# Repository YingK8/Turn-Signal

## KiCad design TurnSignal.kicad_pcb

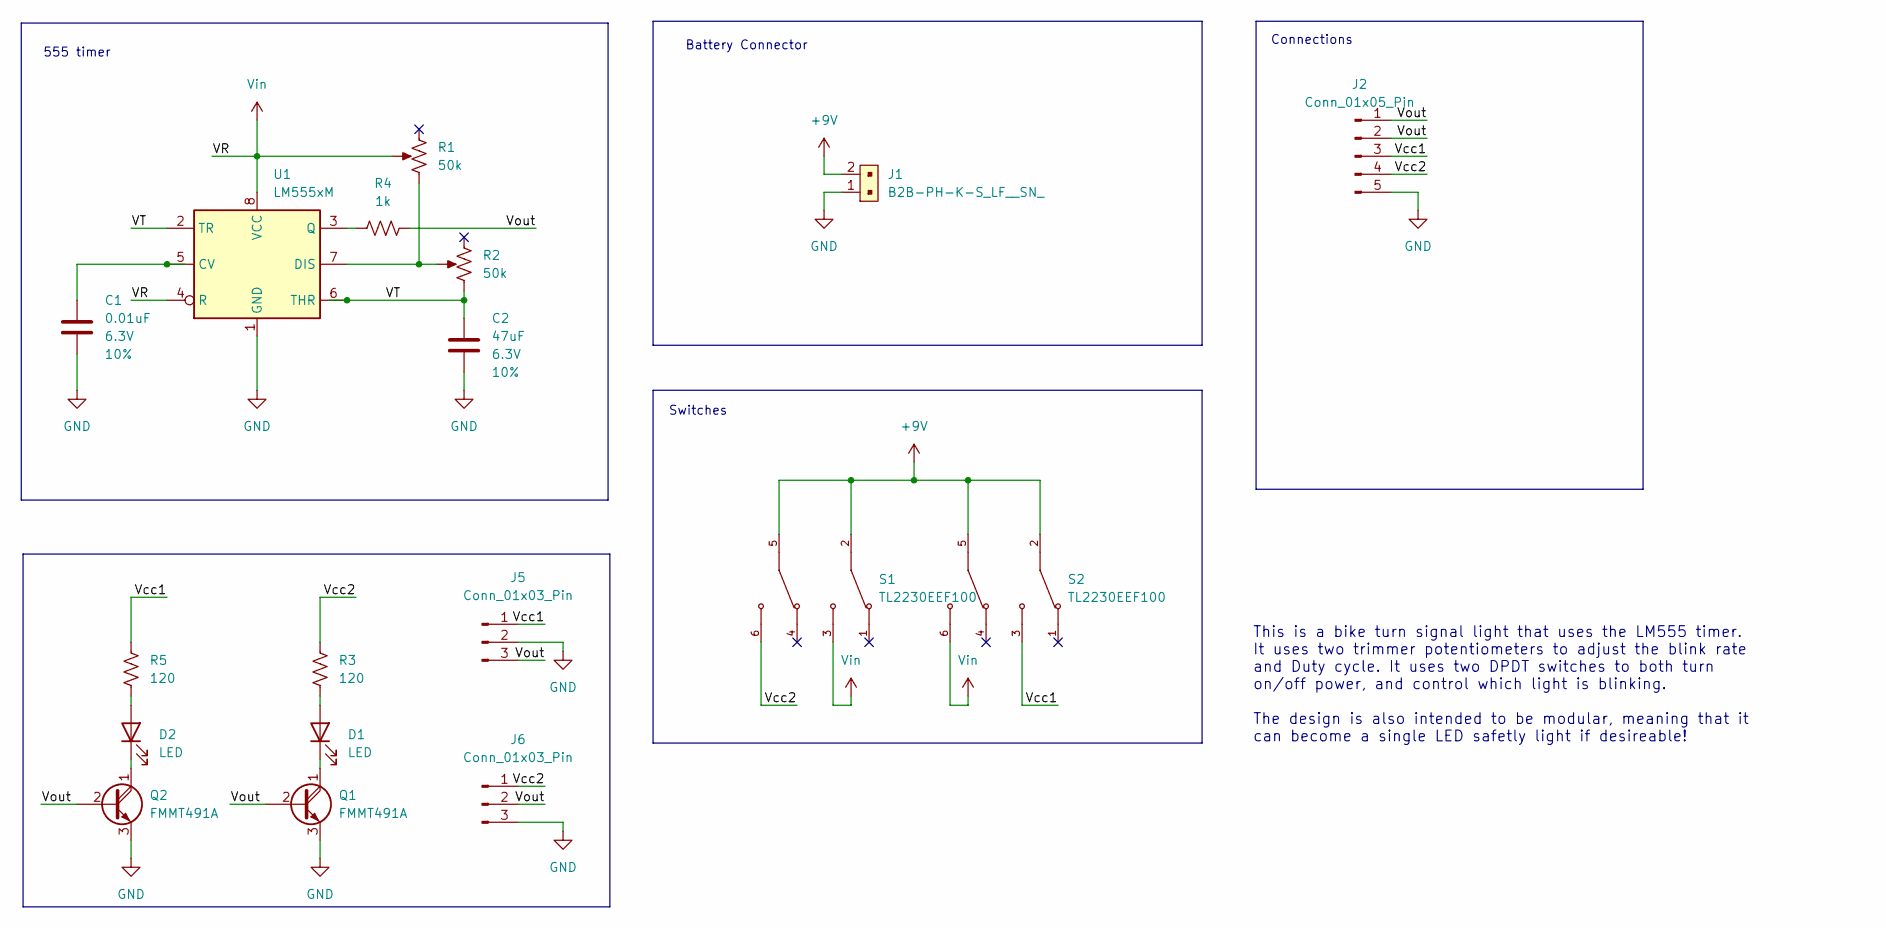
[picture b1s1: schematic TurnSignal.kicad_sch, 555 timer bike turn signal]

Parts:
C1: 0.01uF; C_0805_2012Metric_Pad1.18x1.45mm_HandSolder; Voltage 6.3V; Tolerance 10%
C2: 47uF; C_0805_2012Metric_Pad1.18x1.45mm_HandSolder; Voltage 6.3V; Tolerance 10%
D1, D2: LED; 4-PLCC LED
J1: B2B-PH-K-S_LF__SN_; PinHeader_1x2_P2mm_Drill1mm; MPN B2B-PH-K-S(LF)(SN); Digi-Key_PN 455-1704-ND
J2: Conn_01x05_Pin; PinHeader_1x05_P2.54mm_Vertical
J5, J6: Conn_01x03_Pin; PinHeader_1x03_P2.54mm_Vertical
Q1, Q2: FMMT491A; TO-92_Inline
R1, R2: 50k; TRIM_PV37W103C01B00; Mfg Part# 22AR10K
R3, R5: 120; C_0805_2012Metric_Pad1.18x1.45mm_HandSolder
R4: 1k; C_0805_2012Metric_Pad1.18x1.45mm_HandSolder
S1, S2: TL2230EEF100; SW_TL2230EEF100; PARTREV E
U1: LM555xM; SOIC-8_3.9x4.9mm_P1.27mm

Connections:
+9V: J1.2, S1.2, S1.5, S2.2, S2.5
/VT: C2.1, R2.1, U1.2 (TR), U1.6 (THR)
/Vcc1: J2.3, J5.1, R5.1, S2.3
/Vcc2: J2.4, J6.1, R3.1, S1.6
/Vout: J2.1, J2.2, J5.3, J6.2, Q1.2 (B), Q2.2 (B), R4.2
GND: C1.2, C2.2, J1.1, J2.5, J5.2, J6.3, Q1.3 (E), Q2.3 (E), U1.1 (GND)
unnamed: D1.2 (A), R3.2
unnamed: D1.1 (K), Q1.1 (C)
unnamed: D2.2 (A), R5.2
unnamed: D2.1 (K), Q2.1 (C)
unnamed: C1.1, U1.5 (CV)
unnamed: R1.1, R2.2, U1.7 (DIS)
unnamed: R4.1, U1.3 (Q)
Vin: R1.2, S1.3, S2.6, U1.4 (R), U1.8 (VCC)

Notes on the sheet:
Switches
555 timer
Connections
Battery Connector
This is a bike turn signal light that uses the LM555 timer. It uses two trimmer potentiometers to adjust the blink rate and Duty cycle. It uses two DPDT switches to both turn on/off power, and control which light is blinking. The design is also intended to be modular, meaning that it can become a s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

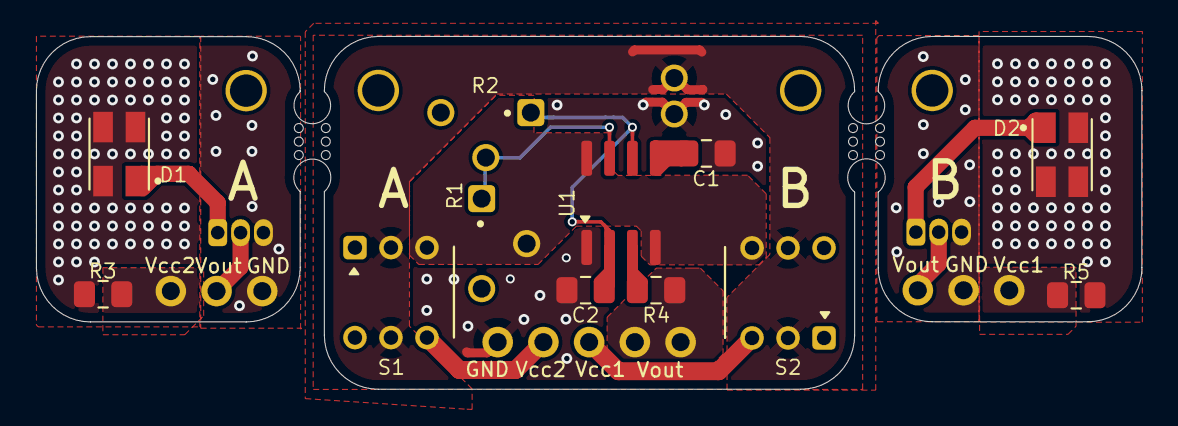
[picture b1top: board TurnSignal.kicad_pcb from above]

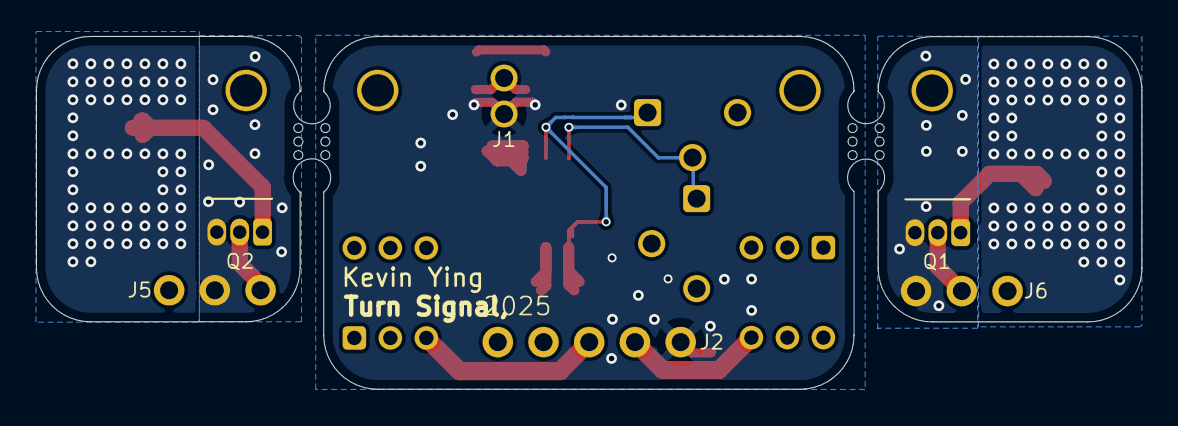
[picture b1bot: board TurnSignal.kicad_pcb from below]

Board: 2 copper layers, 61.4 x 19.6 mm, 20 parts (3 on the bottom side), 14 nets.

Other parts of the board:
mouse-bite-2mm-slot, mouse-bite-2mm-slot#2: VAL**; mouse-bite-2mm-slot

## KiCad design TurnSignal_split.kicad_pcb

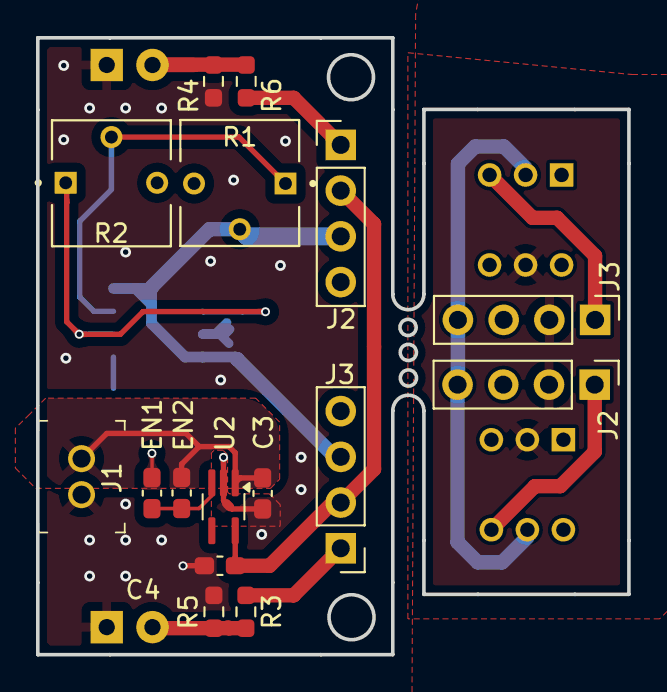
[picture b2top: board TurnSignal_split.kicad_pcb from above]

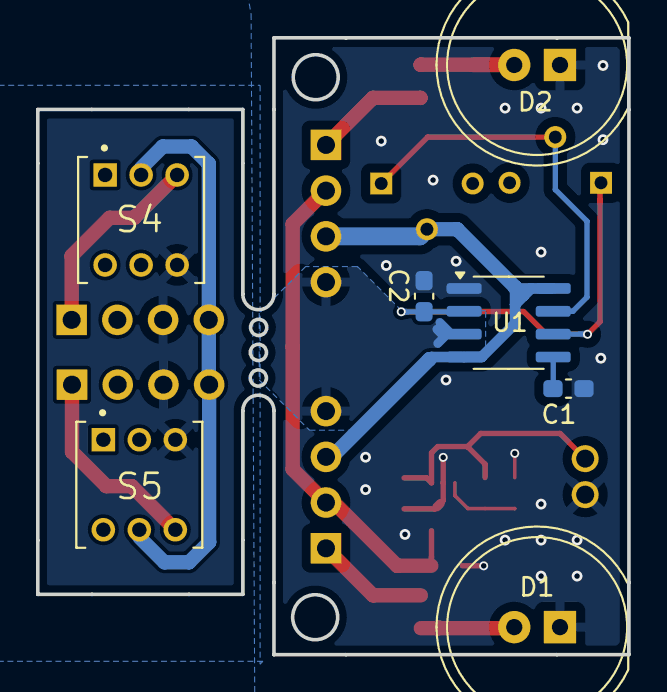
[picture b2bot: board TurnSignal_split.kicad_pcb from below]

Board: 2 copper layers, 32.8 x 34.3 mm, 23 parts (7 on the bottom side), 13 nets.

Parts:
C1: 0.01uF; C_0603_1608Metric_Pad1.08x0.95mm_HandSolder
C2: 470uF; C_0603_1608Metric_Pad1.08x0.95mm_HandSolder
C3, C4: 1uF; C_0603_1608Metric_Pad1.08x0.95mm_HandSolder
D1, D2: LED; LED_D10.0mm
EN1, EN2: 0; C_0603_1608Metric_Pad1.08x0.95mm_HandSolder
J1: B2B-PH-K-S_LF__SN_; PinHeader_1x2_P2mm_Drill1mm
J2, J2#2, J3, J3#2: Conn_01x04_Pin; PinHeader_1x04_P2.54mm_Vertical
R1, R2: 10k; TRIM_3362P-1-103LF
R3, R4, R5, R6: 1.5k; R_0603_1608Metric_Pad0.98x0.95mm_HandSolder
S4, S5: TL2230EEF100; SW_TL2230EEF100
U1: LM555xM; SOIC-8_3.9x4.9mm_P1.27mm
U2: MIC5365-3.3YC5; SOT-353_SC-70-5_Handsoldering

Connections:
+3V3: C4.1, J2.2, J2#2.2, J3.2, J3#2.2, S4.5, S5.2, U2.5 (VOUT)
+3V7: C3.1, EN1.2, J1.2, U2.1 (VIN)
/S1: J3.1, J3#2.1, R3.1, S4.3
/S2: J2.1, J2#2.1, R4.1, S5.6
/VT: C2.1, R2.1, U1.2 (TR), U1.6 (THR)
/Vout: J2.4, J2#2.4, J3.4, J3#2.4, S4.2, S5.5, U1.3 (Q)
GND: C1.2, C2.2, C3.2, C4.2, D1.1 (K), D2.1 (K), EN2.1, J1.1, R5.2, R6.2, U1.1 (GND), U2.2 (GND)
unnamed: D1.2 (A), R3.2, R5.1
unnamed: D2.2 (A), R4.2, R6.1
unnamed: C1.1, U1.5 (CV)
unnamed: R1.1, R2.2, U1.7 (DIS)
unnamed: EN1.1, EN2.2, U2.3 (EN)
Vcc: J2.3, J2#2.3, J3.3, J3#2.3, R1.2, S4.6, S5.3, U1.4 (R), U1.8 (VCC)

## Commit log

2025-06-26 added font
2025-06-27 removed dot
